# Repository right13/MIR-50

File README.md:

I re-designed back in 2012 and old amplifier design published in one of the local magazines for radio amateurs in 1992. The goal was to adapt it to modern (back in 2012) semiconductors and redesign the PCB for DIY audio community in the country.
There is not too much description: I couldnt find the original text. 
 I, with a few other guys managed to sell a few hundreds pcs of the kit and also I made probably another 100 pcs at home by myself. It works as a charm after first powering. Some guys used it as headphone amplifier. 

Some parameters:
Power transistors : TOSHIBA 2SC5200/2SA1943
 Exciters : 2SA1837/2CS4792 or 2SA1930/2SC5171
Pre-amplifier : BD139/140 
Differential stage : BC550/560
Power supply : 2x30V DC 4R 
Output power : 56W
Minimum load impedance : 4R Input sensitivity 
: approx. 1 -1.3V@56W SR waveform speed : 52V/us
Fuses : F2,5A 
Dimension - 130x115 mm
Quiescent current on fuses approx. 120mA (on emitter resistors approx. 13-26mV)

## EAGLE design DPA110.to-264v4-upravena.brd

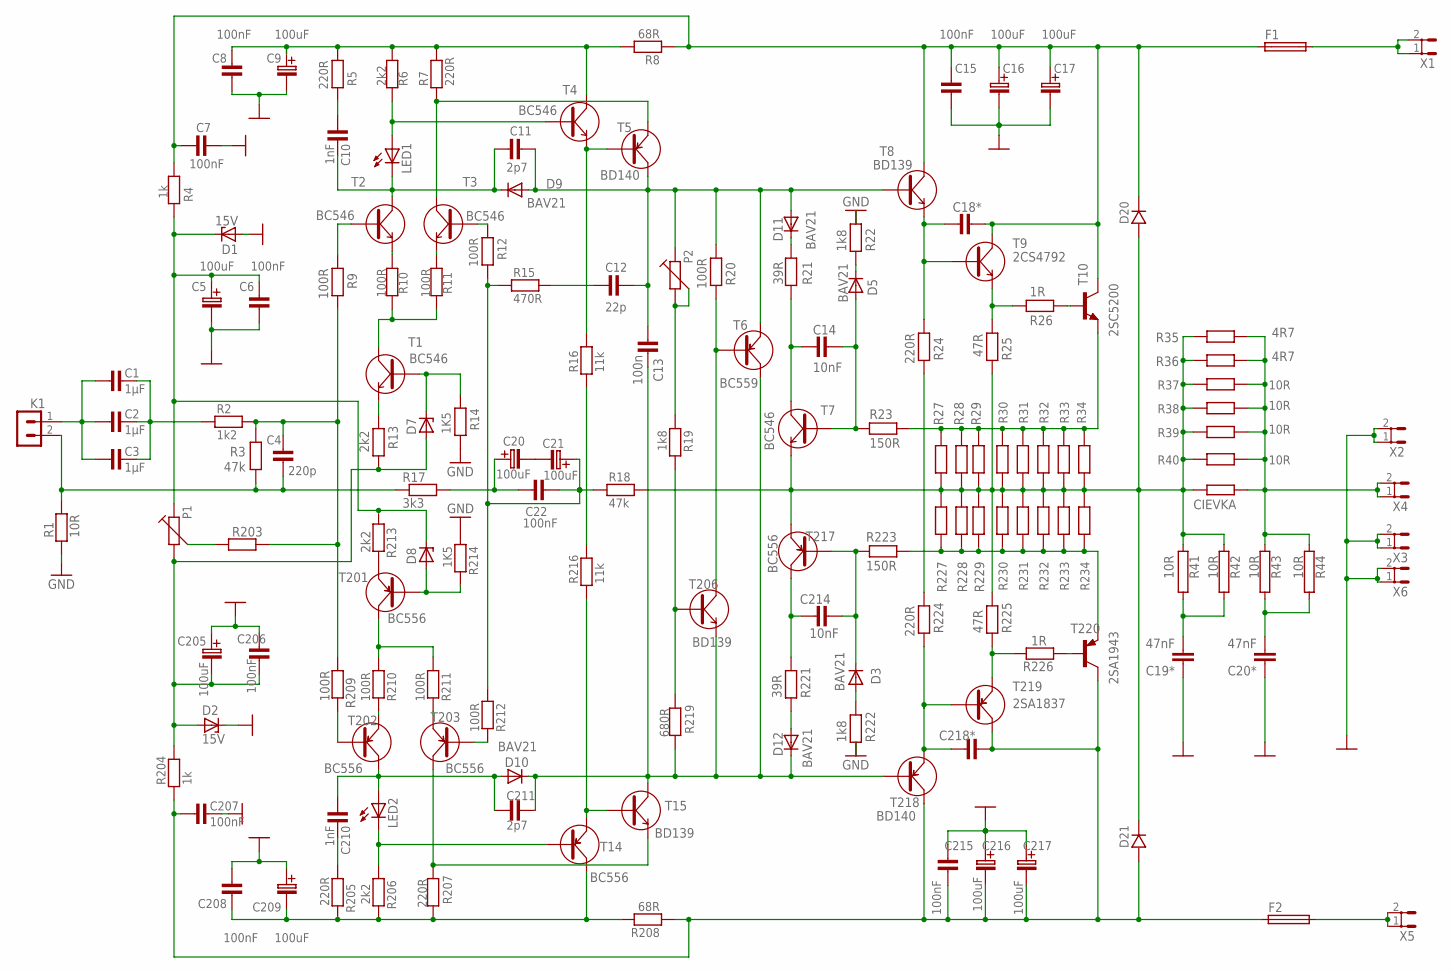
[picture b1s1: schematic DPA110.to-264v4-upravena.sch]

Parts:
C1, C2, C3: 1µF; C-5
C4: 220p; C-5
C5, C205: 100uF; C-EL_2
C6, C7, C8, C15, C22, C206, C207, C208, C215: 100nF; C-5
C9, C16, C17, C20, C21, C209, C216, C217: 100uF; C-EL_3,5
C10, C210: 1nF; C-5
C11, C211: 2p7; C-5
C12: 22p; C-5
C13: 100n; C-5
C14, C214: 10nF; C-5
C18*, C218*: C-KERAMIK_5; C-5
C19*, C20*: 47nF; C150-054X183
CIEVKA: 10R; 0617/22
D1, D2: 15V; SOD81
D3, D5, D9, D10, D11, D12: BAV21; DO35-10
D7, D8: BZX55; DO35Z10
D20, D21: D_10; DO41
F1, F2: SH22,5A
K1: PSH02-02P
LED1, LED2: LED5MM
P1, P2: TRIMR64Y; 64Y
R1, R37, R38, R39, R40: 10R; R-10
R2: 1k2; R-10
R3, R18: 47k; R-10
R4, R204: 1k; R-10
R5, R7, R24, R205, R207, R224: 220R; R-10
R6, R13, R206, R213: 2k2; R-10
R8, R208: 68R; R-10
R9, R12, R20, R209, R212: 100R; R-10
R10, R11, R210, R211: 100R; R-7,5
R14, R214: 1K5; R-10
R15: 470R; R-10
R16, R216: 11k; R-10
R17: 3k3; R-10
R19, R22, R222: 1k8; R-10
R21, R221: 39R; R-10
R23, R223: 150R; R-10
R25, R225: 47R; R-10
R26, R226: 1R; R-10
R27, R28, R29, R227, R228, R229: R__2W; R-_2W
R30, R31, R32, R33, R34, R203, R230, R231, R232, R233, R234: R_10; R-10
R35, R36: 4R7; R-_2W
R41, R42, R43, R44: 10R; AC01
R219: 680R; R-10
T1, T2, T3, T4, T7: BC546; TO-92
T5: BD140; TO-126S
T6: BC559; TO-92
T8, T206: BD139; TO-126
T9: 2CS4792; TO-220
T10: 2SC5200; TO-264
T14, T201, T202, T203, T217: BC556; TO-92
T15: BD139; TO-126S
T218: BD140; TO-126
T219: 2SA1837; TO-220
T220: 2SA1943; TO-264
X1, X2, X3, X4, X5, X6: ST4,8

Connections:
AERT?ZQA??: R16.1, R216.2
D7*: D8.A, R214.2, T201.2 (B)
GND: C5.C- (C_EL-), C6.1, C7.1, C8.1, C9.C- (C_EL-), C15.1, C16.C- (C_EL-), C17.C- (C_EL-), C19*.1, C20*.1, C205.C+ (C_EL+), C206.2, C207.2, C208.2, C209.C+ (C_EL+), C215.2, C216.C+ (C_EL+), C217.C+ (C_EL+), D1.A, D2.C, R1.1, R14.1, R22.2, R214.1, R222.1, X2.1, X2.2, X3.1, X3.2, X6.1, X6.2
unnamed: C1.2, C2.2, C3.2, R2.1
unnamed: C218*.1, R224.1, T218.1 (E), T219.1 (B)
unnamed: C4.2, K1.2, R1.2, R3.1, R17.1
unnamed: R13.2, T1.3 (E)
unnamed: C4.1, R2.2, R3.2, R9.1, R203.2, R209.1
unnamed: R9.2, T2.2 (B)
unnamed: R10.2, T2.3 (E)
unnamed: D7.C, R14.2, T1.2 (B)
unnamed: C205.C- (C_EL-), C206.1, D2.A, D7.A, P1.2, R13.1, R204.2
unnamed: P1.3, R203.1
unnamed: R213.2, T201.3 (E)
unnamed: R209.2, T202.2 (B)
unnamed: R210.2, T202.3 (E)
unnamed: R12.2, T3.2 (B)
unnamed: D5.C, R22.1
unnamed: R212.2, T203.2 (B)
unnamed: C7.2, C15.2, C16.C+ (C_EL+), C17.C+ (C_EL+), C18*.2, D20.K, F1.1, R4.2, R8.1, T8.2 (C), T9.2 (C), T10.C
unnamed: C21.C+ (C_EL+), C22.1, R12.1, R15.1, R18.1, R212.1
unnamed: C20.C- (C_EL-), C21.C- (C_EL-)
unnamed: C8.2, R5.2, R6.2, R7.1, R8.2, T4.1 (C)
unnamed: C20.C+ (C_EL+), C22.2, R17.2
unnamed: C10.1, R5.1
unnamed: C10.2, C11.1, D9.C, LED1.K (C), T2.1 (C)
unnamed: LED2.K (C), R206.1, T14.2 (B)
unnamed: C19*.2, R41.2, R42.2
unnamed: C18*.1, R24.2, T8.1 (E), T9.1 (B)
unnamed: LED1.A, R6.1, T4.2 (B)
unnamed: C210.2, R205.1
unnamed: R7.2, T3.1 (C), T5.1 (E)
unnamed: C208.1, C209.C- (C_EL-), R205.2, R206.2, R207.1, R208.2, T14.1 (C)
unnamed: R207.2, T15.1 (E), T203.1 (C)
unnamed: R16.2, T4.3 (E), T5.3 (B)
unnamed: C12.1, R15.2
unnamed: C11.2, C12.2, C13.1, D9.A, D11.A, P2.1, R20.2, T5.2 (C), T6.3 (E), T8.3 (B)
unnamed: P2.2, P2.3, R19.1
unnamed: C13.2, C211.2, D10.C, D12.C, R219.1, T6.1 (C), T15.2 (C), T206.1 (E), T218.3 (B)
unnamed: R19.2, R219.2, T206.3 (B)
unnamed: R20.1, T6.2 (B), T206.2 (C)
unnamed: R11.2, T3.3 (E)
unnamed: C214.2, D3.C, R223.2, T217.2 (B)
unnamed: D11.C, R21.1
unnamed: C14.1, R21.2, T7.1 (C)
unnamed: D12.A, R221.1
unnamed: C214.1, R221.2, T217.1 (C)
unnamed: D3.A, R222.2
unnamed: C14.2, D5.A, R23.1, T7.2 (B)
unnamed: R10.1, R11.1, T1.1 (C)
unnamed: R24.1, R224.2
unnamed: R211.2, T203.3 (E)
unnamed: C207.1, C215.1, C216.C- (C_EL-), C217.C- (C_EL-), C218*.2, D21.A, F2.1, R204.1, R208.1, T218.2 (C), T219.2 (C), T220.C
unnamed: R210.1, R211.1, T201.1 (C)
unnamed: R25.2, R26.1, T9.3 (E)
unnamed: R225.1, R226.2, T219.3 (E)
unnamed: R23.2, R27.2, R28.2, R29.2, R30.2, R31.2, R32.2, R33.2, R34.2, T10.E
unnamed: R223.1, R227.1, R228.1, R229.1, R230.1, R231.1, R232.1, R233.1, R234.1, T220.E
unnamed: F1.2, X1.1, X1.2
unnamed: R26.2, T10.B
unnamed: F2.2, X5.1, X5.2
unnamed: R226.1, T220.B
unnamed: C210.1, C211.1, D10.A, LED2.A, T202.1 (C)
unnamed: CIEVKA.1, D20.A, D21.K, R18.2, R25.1, R27.1, R28.1, R29.1, R30.1, R31.1, R32.1, R33.1, R34.1, R35.1, R36.1, R37.2, R38.2, R39.2, R40.2, R41.1, R42.1, R225.2, R227.2, R228.2, R229.2, R230.2, R231.2, R232.2, R233.2, R234.2, T7.3 (E), T217.3 (E)
unnamed: R216.1, T14.3 (E), T15.3 (B)
unnamed: C5.C+ (C_EL+), C6.2, D1.C, D8.C, P1.1, R4.1, R213.1
unnamed: C20*.2, R43.2, R44.2
unnamed: C1.1, C2.1, C3.1, K1.1
OUT: CIEVKA.2, R35.2, R36.2, R37.1, R38.1, R39.1, R40.1, R43.1, R44.1, X4.1, X4.2

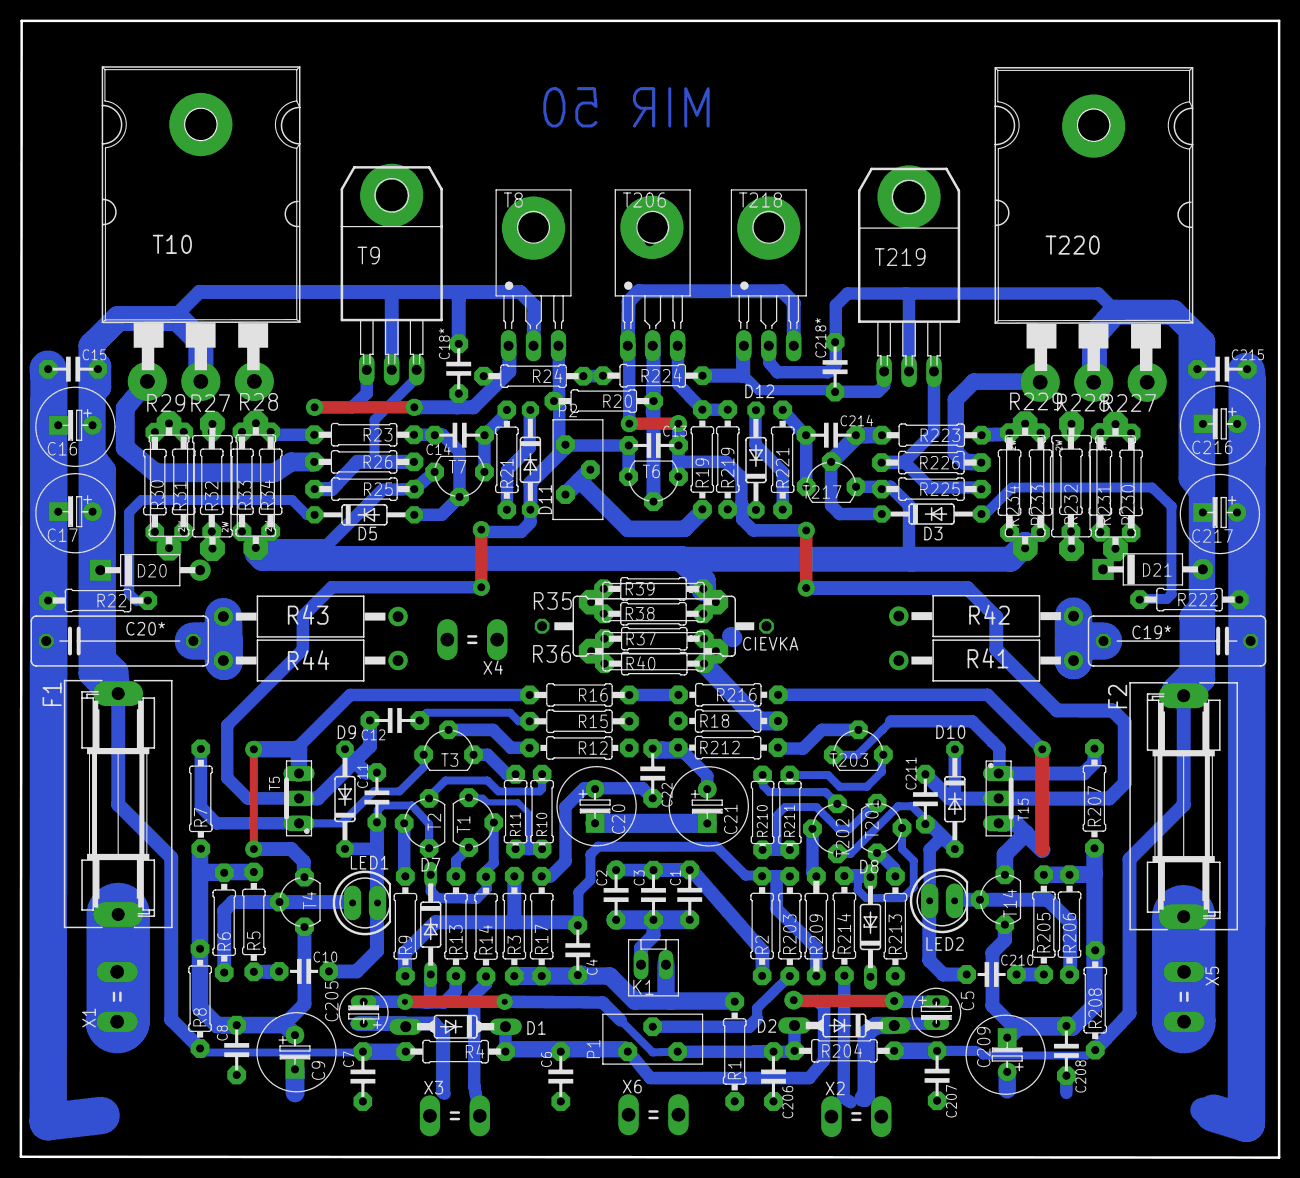
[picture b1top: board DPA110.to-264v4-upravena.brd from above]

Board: 2 copper layers, 128.2 x 115.8 mm, 153 parts (0 on the bottom side), 69 nets.
